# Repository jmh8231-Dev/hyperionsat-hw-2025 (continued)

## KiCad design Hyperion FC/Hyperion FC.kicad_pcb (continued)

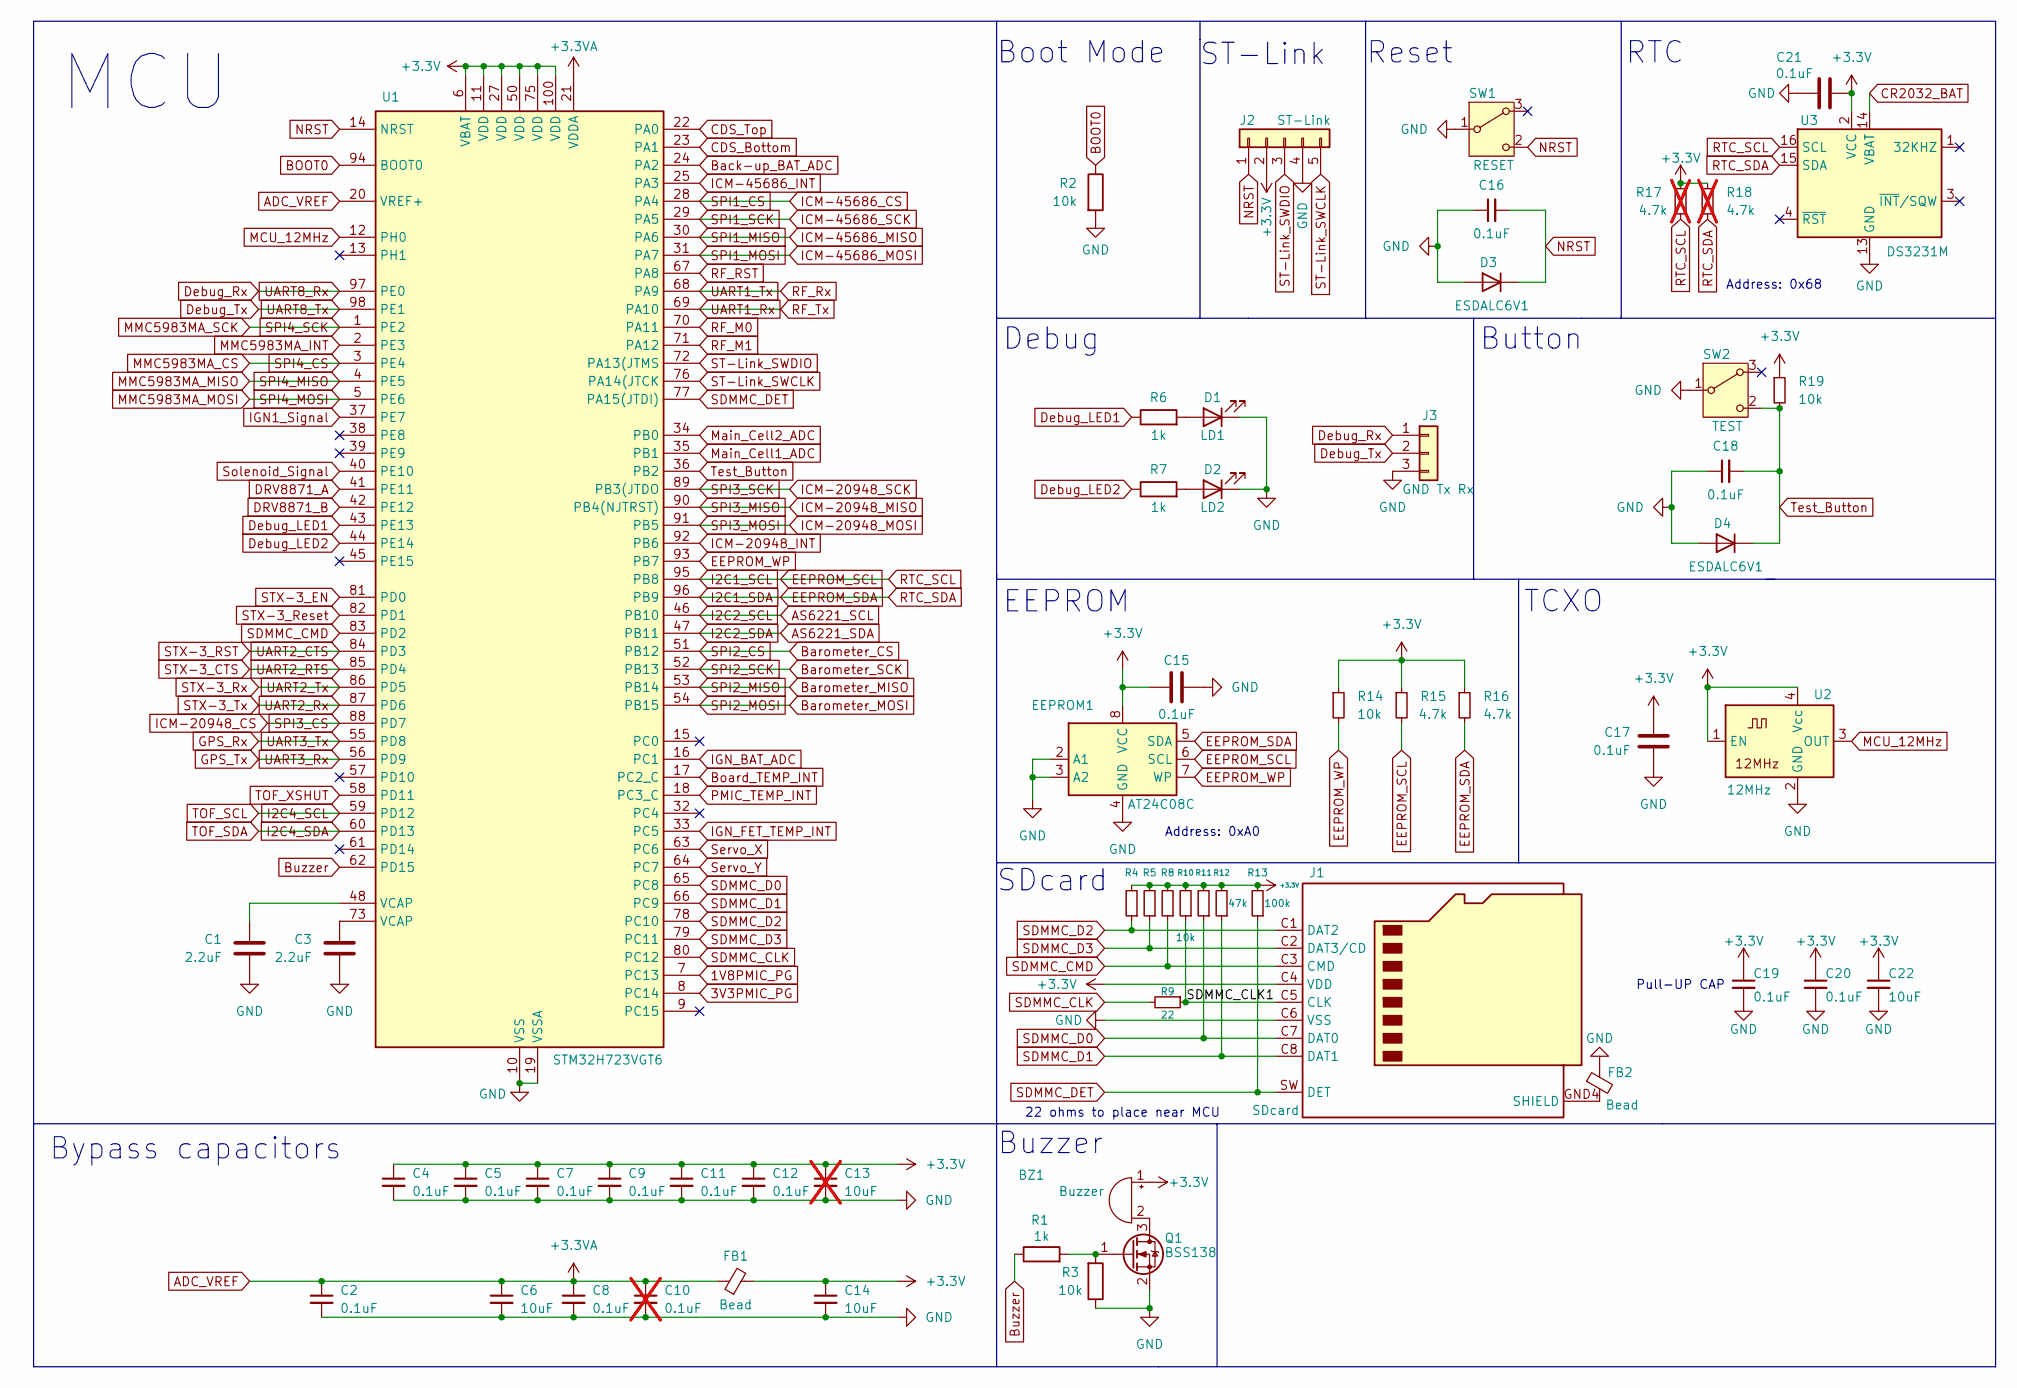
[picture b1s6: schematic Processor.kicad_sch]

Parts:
BZ1: Buzzer; XDCR_SMTB-0827-TW-R
C1, C3: 2.2uF; C_0603_1608Metric
C2, C4, C5, C7, C8, C9, C11, C12, C15, C16, C17, C18, C19, C20, C21: 0.1uF; C_0603_1608Metric
C6, C14, C22: 10uF; C_0805_2012Metric
C10: 0.1uF; C_0603_1608Metric; not fitted
C13: 10uF; C_0805_2012Metric; not fitted
D1: LD1; LED_0805_2012Metric
D2: LD2; LED_0805_2012Metric
D3, D4: ESDALC6V1; D_SOD-882D
EEPROM1: AT24C08C; SOIC-8_3.9x4.9mm_P1.27mm
FB1, FB2: Bead; L_0603_1608Metric
J1: SDcard; JAE_ST1W008S4TR2000
J2: ST-Link; PinHeader_1x05_P2.54mm_Vertical
J3: GND Tx Rx; PinHeader_1x03_P2.54mm_Vertical
Q1: BSS138; SOT-23
R1, R6, R7: 1k; R_0603_1608Metric
R2, R3, R10, R14, R19: 10k; R_0603_1608Metric
R4, R5, R8, R11, R12: 47k; R_0603_1608Metric
R9: 22; R_0402_1005Metric
R13: 100k; R_0603_1608Metric
R15, R16: 4.7k; R_0603_1608Metric
R17, R18: 4.7k; R_0603_1608Metric; not fitted
SW1: RESET; TLSMDT3C020GLFS
SW2: TEST; TLSMDT3C020GLFS
U1: STM32H723VGT6; LQFP-100_14x14mm_P0.5mm
U2: 12MHz; ECS-TXO-2016
U3: DS3231M; SOIC-16W_7.5x10.3mm_P1.27mm

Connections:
1V8PMIC_PG: U1.7 (PC13); also elsewhere on the board
3V3PMIC_PG: U1.8 (PC14); also elsewhere on the board
+3.3V: BZ1.1 (-), C4.1, C5.1, C7.1, C9.1, C11.1, C12.1, C13.1, C14.1, C15.1, C17.1, C19.1, C20.1, C21.2, C22.1, EEPROM1.8 (VCC), FB1.2, J1.C4 (VDD), J2.2, R4.2, R5.2, R8.2, R10.2, R11.2, R12.2, R13.2, R14.1, R15.1, R16.1, R17.1, R18.1, R19.1, U1.6 (VBAT), U1.11 (VDD), U1.27 (VDD), U1.50 (VDD), U1.75 (VDD), U1.100 (VDD), U2.1 (EN), U2.4 (Vcc), U3.2 (VCC); also elsewhere on the board
/Processor/SDMMC_CLK1: J1.C5 (CLK), R9.1, R10.1
ADC_VREF: C2.1, C6.1, C8.1, C10.1, FB1.1, U1.20 (VREF+), U1.21 (VDDA)
AS6221_SCL: U1.46 (PB10); also elsewhere on the board
AS6221_SDA: U1.47 (PB11); also elsewhere on the board
BOOT0: R2.1, U1.94 (BOOT0)
Back-up_BAT_ADC: U1.24 (PA2); also elsewhere on the board
Barometer_CS: U1.51 (PB12); also elsewhere on the board
Barometer_MISO: U1.53 (PB14); also elsewhere on the board
Barometer_MOSI: U1.54 (PB15); also elsewhere on the board
Barometer_SCK: U1.52 (PB13); also elsewhere on the board
Board_TEMP_INT: U1.17 (PC2_C); also elsewhere on the board
Buzzer: R1.1, U1.62 (PD15)
CDS_Bottom: U1.23 (PA1); also elsewhere on the board
CDS_Top: U1.22 (PA0); also elsewhere on the board
CR2032_BAT: U3.14 (VBAT); also elsewhere on the board
DRV8871_A: U1.41 (PE11); also elsewhere on the board
DRV8871_B: U1.42 (PE12); also elsewhere on the board
Debug_LED1: R6.1, U1.43 (PE13)
Debug_LED2: R7.1, U1.44 (PE14)
Debug_Rx: J3.1, U1.97 (PE0)
Debug_Tx: J3.2, U1.98 (PE1)
EEPROM_SCL: EEPROM1.6 (SCL), R15.2, R17.2, U1.95 (PB8), U3.16 (SCL)
EEPROM_SDA: EEPROM1.5 (SDA), R16.2, R18.2, U1.96 (PB9), U3.15 (SDA)
EEPROM_WP: EEPROM1.7 (WP), R14.2, U1.93 (PB7)
GND: C1.2, C2.2, C3.2, C4.2, C5.2, C6.2, C7.2, C8.2, C9.2, C10.2, C11.2, C12.2, C13.2, C14.2, C15.2, C16.1, C17.2, C18.1, C19.2, C20.2, C21.1, C22.2, D1.1 (K), D2.1 (K), D3.2 (A), D4.2 (A), EEPROM1.2 (A1), EEPROM1.3 (A2), EEPROM1.4 (GND), FB2.1, J1.C6 (VSS), J2.4, J3.3, Q1.2 (S), R2.2, R3.1, SW1.1 (B), SW2.1 (B), U1.10 (VSS), U1.19 (VSSA), U1.26 (VSS), U1.49 (VSS), U1.74 (VSS), U1.99 (VSS), U2.2 (GND), U3.5 (GND), U3.6 (GND), U3.7 (GND), U3.8 (GND), U3.9 (GND), U3.10 (GND), U3.11 (GND), U3.12 (GND), U3.13 (GND); also elsewhere on the board
GPS_Rx: U1.55 (PD8); also elsewhere on the board
GPS_Tx: U1.56 (PD9); also elsewhere on the board
I2C4_SCL: U1.59 (PD12); also elsewhere on the board
I2C4_SDA: U1.60 (PD13); also elsewhere on the board
ICM-20948_CS: U1.88 (PD7); also elsewhere on the board
ICM-20948_INT: U1.92 (PB6); also elsewhere on the board
ICM-20948_MISO: U1.90 (PB4(NJTRST)); also elsewhere on the board
ICM-20948_MOSI: U1.91 (PB5); also elsewhere on the board
ICM-20948_SCK: U1.89 (PB3(JTDO); also elsewhere on the board
ICM-45686_CS: U1.28 (PA4); also elsewhere on the board
ICM-45686_INT: U1.25 (PA3); also elsewhere on the board
ICM-45686_MISO: U1.30 (PA6); also elsewhere on the board
ICM-45686_MOSI: U1.31 (PA7); also elsewhere on the board
ICM-45686_SCK: U1.29 (PA5); also elsewhere on the board
IGN1_Signal: U1.37 (PE7); also elsewhere on the board
IGN_BAT_ADC: U1.16 (PC1); also elsewhere on the board
IGN_FET_TEMP_INT: U1.33 (PC5); also elsewhere on the board
MCU_12MHz: U1.12 (PH0), U2.3 (OUT)
MMC5983MA_CS: U1.3 (PE4); also elsewhere on the board
MMC5983MA_INT: U1.2 (PE3); also elsewhere on the board
MMC5983MA_MISO: U1.4 (PE5); also elsewhere on the board
MMC5983MA_MOSI: U1.5 (PE6); also elsewhere on the board
MMC5983MA_SCK: U1.1 (PE2); also elsewhere on the board
Main_Cell1_ADC: U1.35 (PB1); also elsewhere on the board
Main_Cell2_ADC: U1.34 (PB0); also elsewhere on the board
NRST: C16.2, D3.1 (K), J2.1, SW1.2 (C), U1.14 (NRST)
unnamed: BZ1.2 (+), Q1.3 (D)
unnamed: C1.1, U1.48 (VCAP)
unnamed: C3.1, U1.73 (VCAP)
unnamed: D1.2 (A), R6.2
unnamed: D2.2 (A), R7.2
unnamed: FB2.2, J1.GND4 (SHIELD)
unnamed: Q1.1 (G), R1.2, R3.2
PMIC_TEMP_INT: U1.18 (PC3_C); also elsewhere on the board
RF_M0: U1.70 (PA11); also elsewhere on the board
RF_M1: U1.71 (PA12); also elsewhere on the board
RF_RST: U1.67 (PA8); also elsewhere on the board
RF_Rx: U1.68 (PA9); also elsewhere on the board
RF_Tx: U1.69 (PA10); also elsewhere on the board
SDMMC_CLK: R9.2, U1.80 (PC12)
SDMMC_CMD: J1.C3 (CMD), R8.1, U1.83 (PD2)
SDMMC_D0: J1.C7 (DAT0), R11.1, U1.65 (PC8)
SDMMC_D1: J1.C8 (DAT1), R12.1, U1.66 (PC9)
SDMMC_D2: J1.C1 (DAT2), R4.1, U1.78 (PC10)
SDMMC_D3: J1.C2 (DAT3/CD), R5.1, U1.79 (PC11)
SDMMC_DET: J1.SW (DET), R13.1, U1.77 (PA15(JTDI))
ST-Link_SWCLK: J2.5, U1.76 (PA14(JTCK)
ST-Link_SWDIO: J2.3, U1.72 (PA13(JTMS)
STX-3_CTS: U1.85 (PD4); also elsewhere on the board
STX-3_EN: U1.81 (PD0); also elsewhere on the board
STX-3_RST: U1.84 (PD3); also elsewhere on the board
STX-3_Reset: U1.82 (PD1); also elsewhere on the board
STX-3_Rx: U1.86 (PD5); also elsewhere on the board
STX-3_Tx: U1.87 (PD6); also elsewhere on the board
Servo_X: U1.63 (PC6); also elsewhere on the board
Servo_Y: U1.64 (PC7); also elsewhere on the board
Solenoid_Signal: U1.40 (PE10); also elsewhere on the board
TOF_XSHUT: U1.58 (PD11); also elsewhere on the board
Test_Button: C18.2, D4.1 (K), R19.2, SW2.2 (C), U1.36 (PB2)

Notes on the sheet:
Address: 0x68
Bypass capacitors
Address: 0xA0
EEPROM
22 ohms to place near MCU
ST-Link
Buzzer
Boot Mode
RTC
Debug
Button
SDcard
Pull-UP CAP
Reset
MCU
TCXO

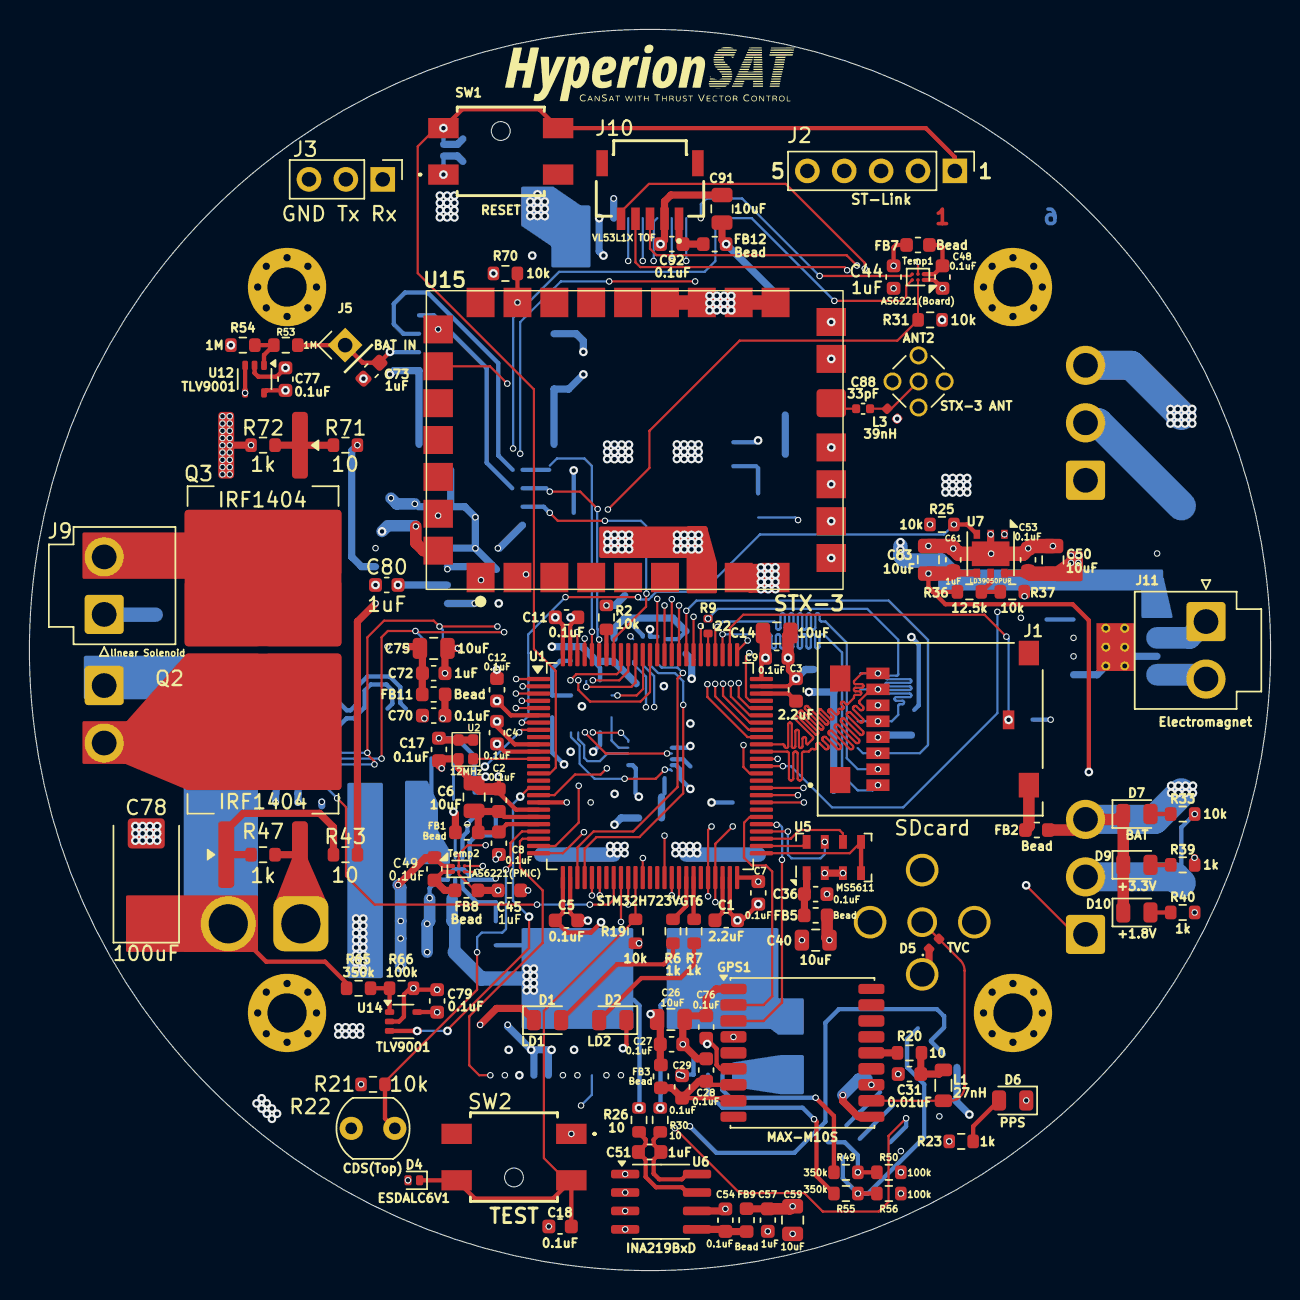
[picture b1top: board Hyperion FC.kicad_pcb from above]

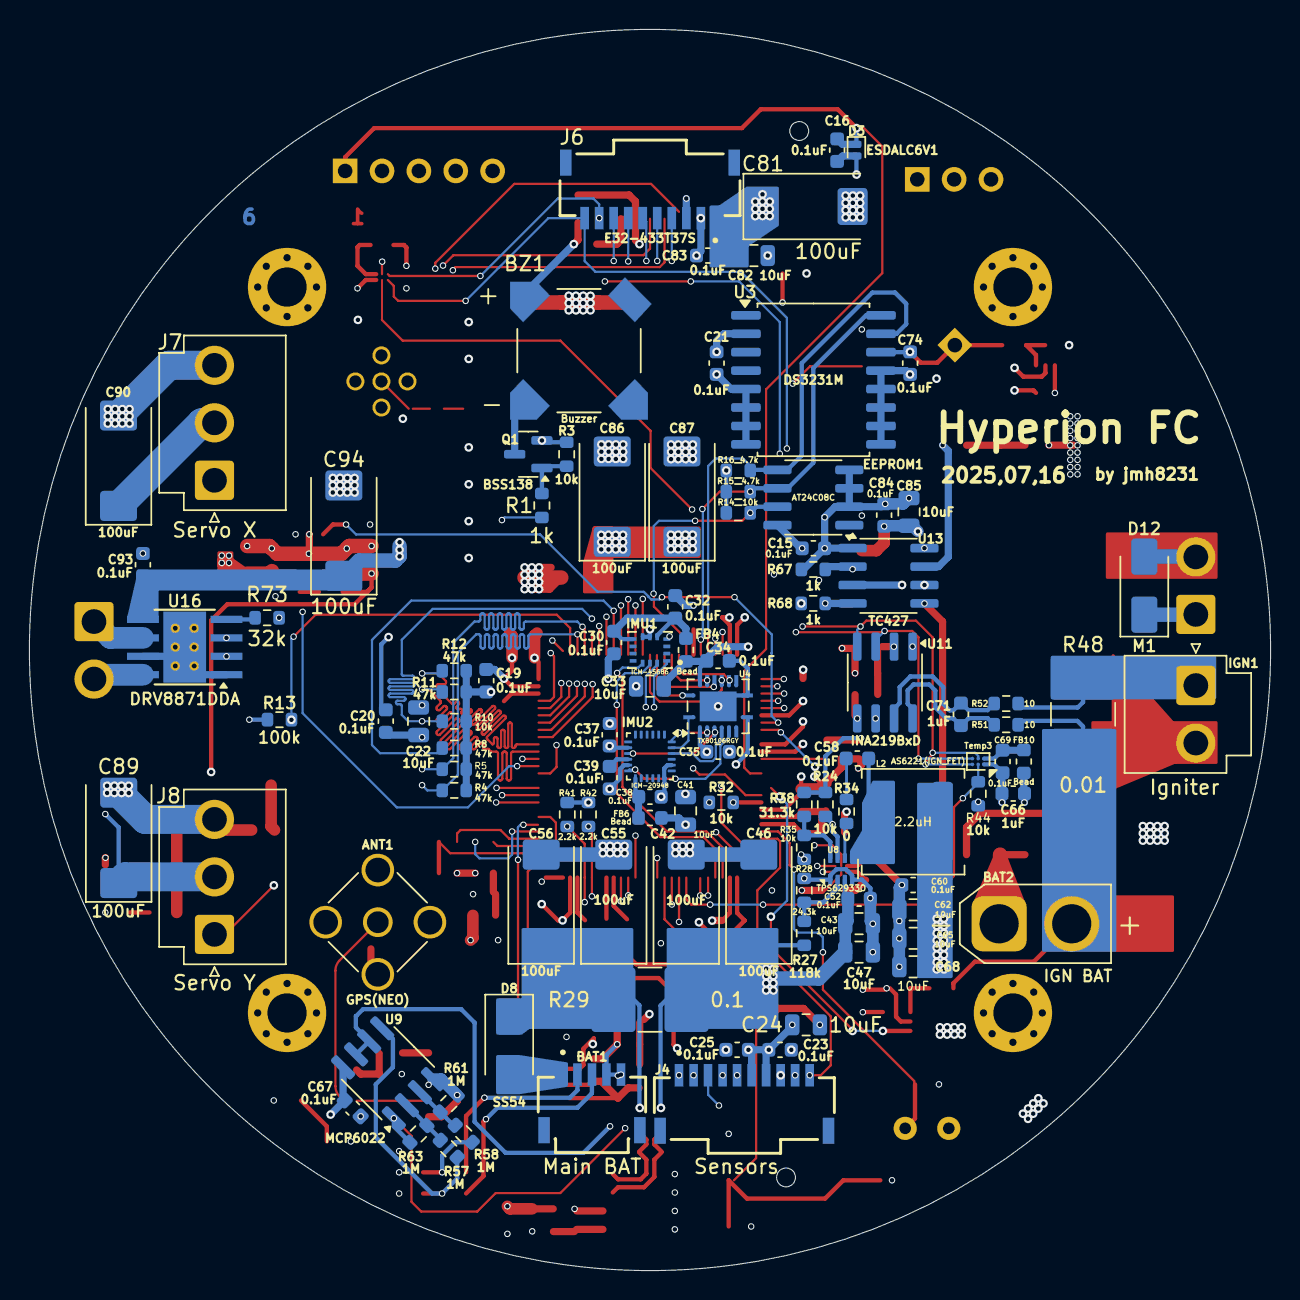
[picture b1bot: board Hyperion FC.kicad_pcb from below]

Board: 6 copper layers, 85.5 x 85.5 mm, 229 parts (107 on the bottom side), 146 nets.

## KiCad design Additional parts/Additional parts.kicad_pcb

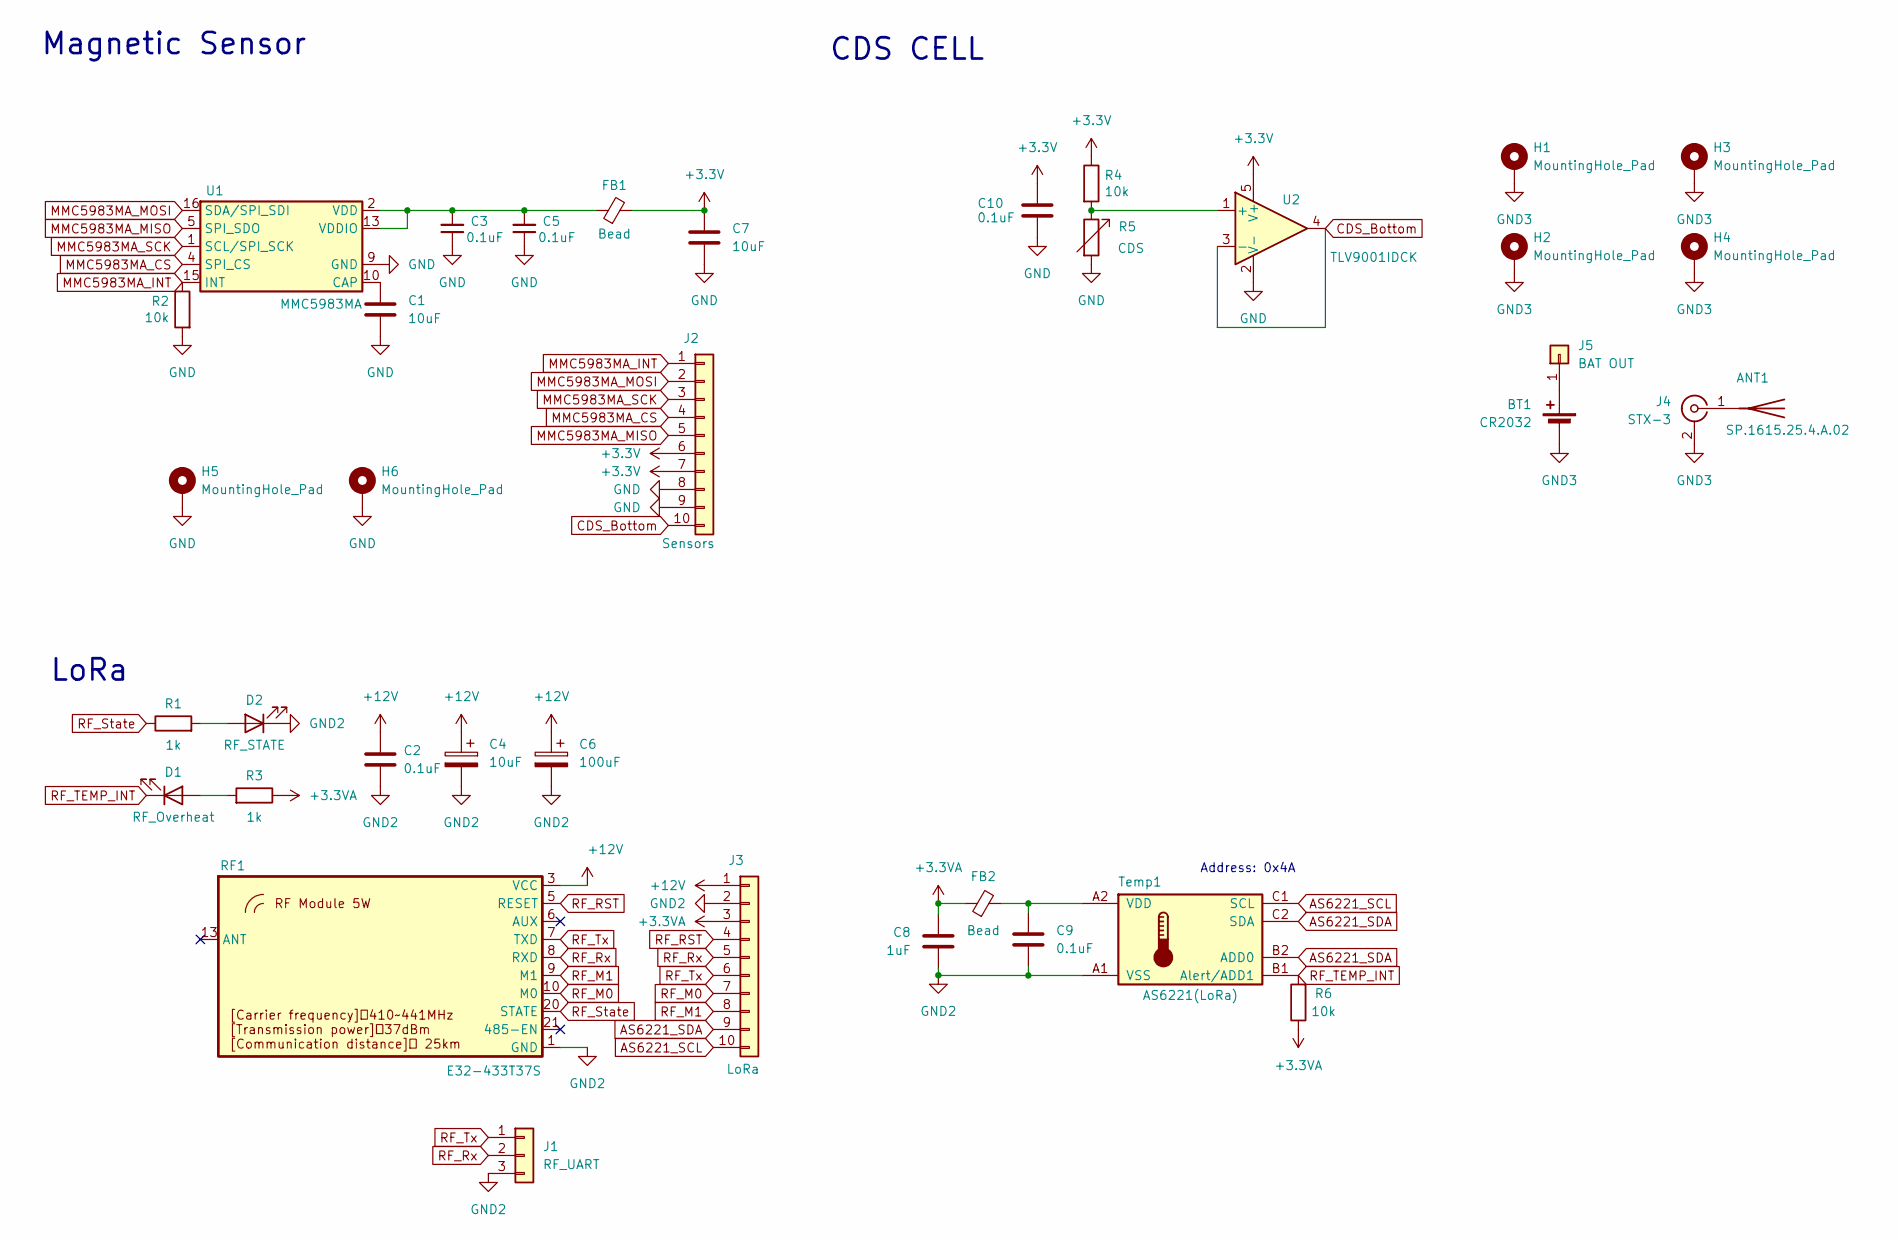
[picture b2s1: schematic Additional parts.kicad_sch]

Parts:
ANT1: SP.1615.25.4.A.02
BT1: CR2032; BAT-HLD-001
C1, C4, C7: 10uF; C_0805_2012Metric
C2, C3, C5, C9, C10: 0.1uF; C_0603_1608Metric
C6: 100uF; CP_EIA-7343-43_Kemet-X
C8: 1uF; C_0603_1608Metric
D1: RF_Overheat; LED_0805_2012Metric
D2: RF_STATE; LED_0805_2012Metric
FB1, FB2: Bead; L_0603_1608Metric
H1, H2, H3, H4, H5, H6: MountingHole_Pad; MountingHole_2.7mm_M2.5_Pad_Via
J1: RF_UART; PinHeader_1x03_P2.54mm_Vertical
J2: Sensors; SAMTEC_T1M-10-F-SH-L-K
J3: LoRa; SAMTEC_T1M-10-F-SH-L-K
J4: STX-3; LINX_CONMMCX001-SMD-T
J5: BAT OUT; PinHeader_1x01_P2.54mm_Vertical
R1, R3: 1k; R_0603_1608Metric
R2, R4, R6: 10k; R_0603_1608Metric
R5: CDS; R_LDR_5.0x4.1mm_P3mm_Vertical
RF1: E32-433T37S
Temp1: AS6221(LoRa); WLCSP-6_1.4x1.0mm_P0.4mm
U1: MMC5983MA; LGA-16_3x3mm_P0.5mm
U2: TLV9001IDCK; SOT-353_SC-70-5

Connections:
+3.3V: C7.1, C10.1, FB1.2, J2.6, J2.7, R4.1, U2.5 (V+)
+3.3VA: C8.2, FB2.1, J3.3, R3.1, R6.1
+12V: C2.1, C4.1, C6.1, J3.1, RF1.3 (VCC), RF1.4 (VCC)
AS6221_SCL: J3.10, Temp1.C1 (SCL)
AS6221_SDA: J3.9, Temp1.B2 (ADD0), Temp1.C2 (SDA)
CDS_Bottom: J2.10, U2.3 (-), U2.4
GND: C1.2, C3.1, C5.1, C7.2, C10.2, H5.1, H6.1, J2.8, J2.9, R2.2, R5.2, U1.9 (GND), U1.11 (GND), U2.2 (V-)
GND2: C2.2, C4.2, C6.2, C8.1, C9.2, D2.1 (K), J1.3, J3.2, RF1.1 (GND), RF1.2 (GND), RF1.11 (GND), RF1.12 (GND), RF1.14 (GND), RF1.15 (GND), RF1.16 (GND), RF1.17 (GND), RF1.18 (GND), RF1.19 (GND), RF1.27 (GND), Temp1.A1 (VSS)
GND3: BT1.2 (-), H1.1, H2.1, H3.1, H4.1, J4.2 (Ext)
MMC5983MA_CS: J2.4, U1.4 (SPI_CS)
MMC5983MA_INT: J2.1, R2.1, U1.15 (INT)
MMC5983MA_MISO: J2.5, U1.5 (SPI_SDO)
MMC5983MA_MOSI: J2.2, U1.16 (SDA/SPI_SDI)
MMC5983MA_SCK: J2.3, U1.1 (SCL/SPI_SCK)
unnamed: ANT1.1 (A), J4.1 (In)
unnamed: BT1.1 (+), J5.1
unnamed: D1.2 (A), R3.2
unnamed: D2.2 (A), R1.2
unnamed: C9.1, FB2.2, Temp1.A2 (VDD)
unnamed: C1.1, U1.10 (CAP)
unnamed: C3.2, C5.2, FB1.1, U1.2 (VDD), U1.13 (VDDIO)
unnamed: R4.2, R5.1, U2.1 (+)
RF_M0: J3.7, RF1.10 (M0)
RF_M1: J3.8, RF1.9 (M1)
RF_RST: J3.4, RF1.5 (RESET)
RF_Rx: J1.2, J3.5, RF1.8 (RXD)
RF_State: R1.1, RF1.20 (STATE)
RF_TEMP_INT: D1.1 (K), R6.2, Temp1.B1 (Alert/ADD1)
RF_Tx: J1.1, J3.6, RF1.7 (TXD)

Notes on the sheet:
Address: 0x4A
LoRa
Magnetic Sensor
CDS CELL

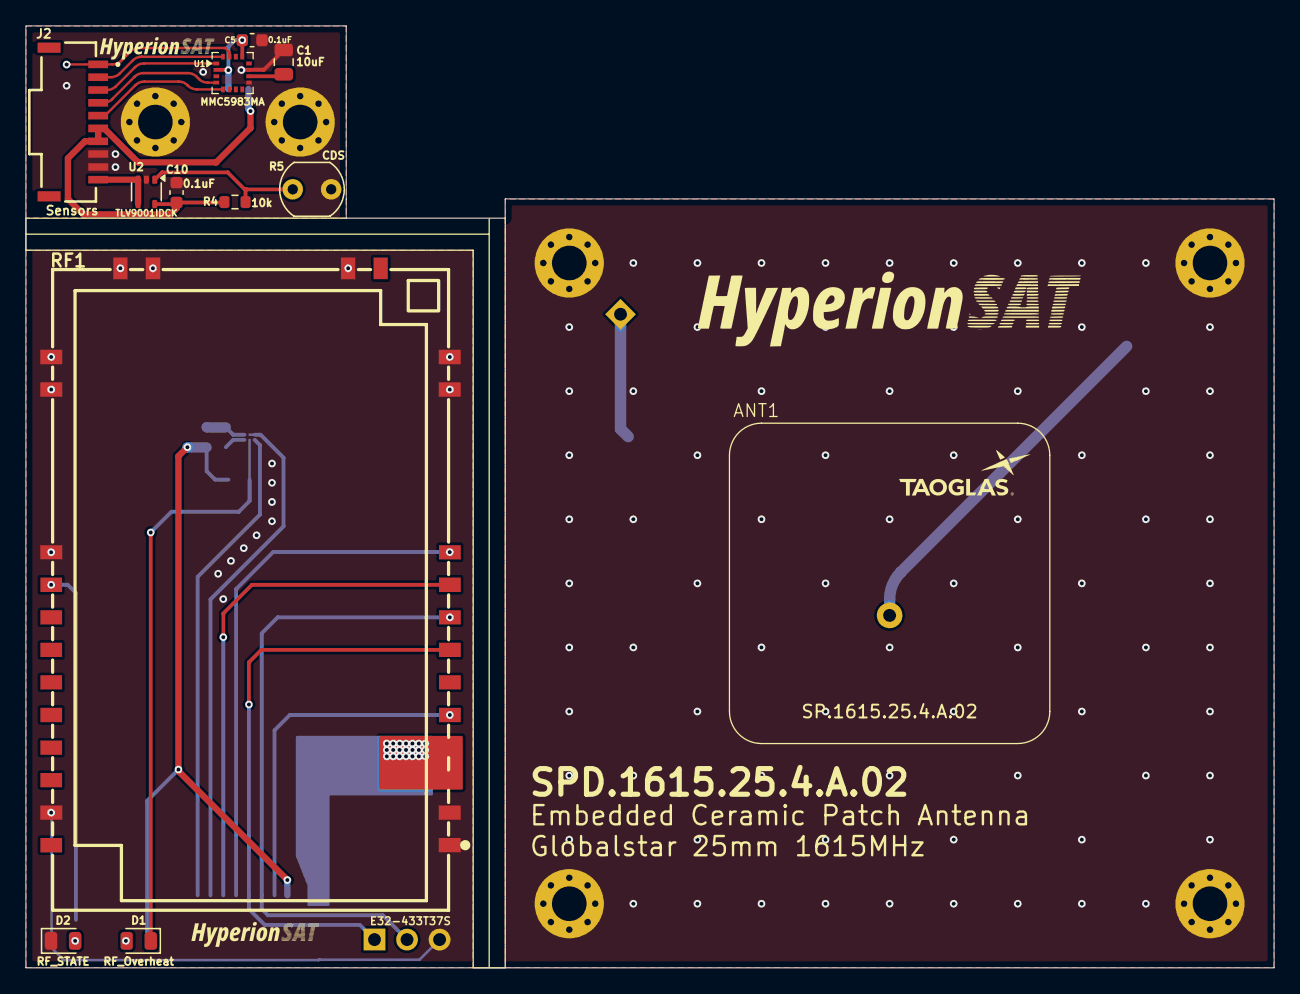
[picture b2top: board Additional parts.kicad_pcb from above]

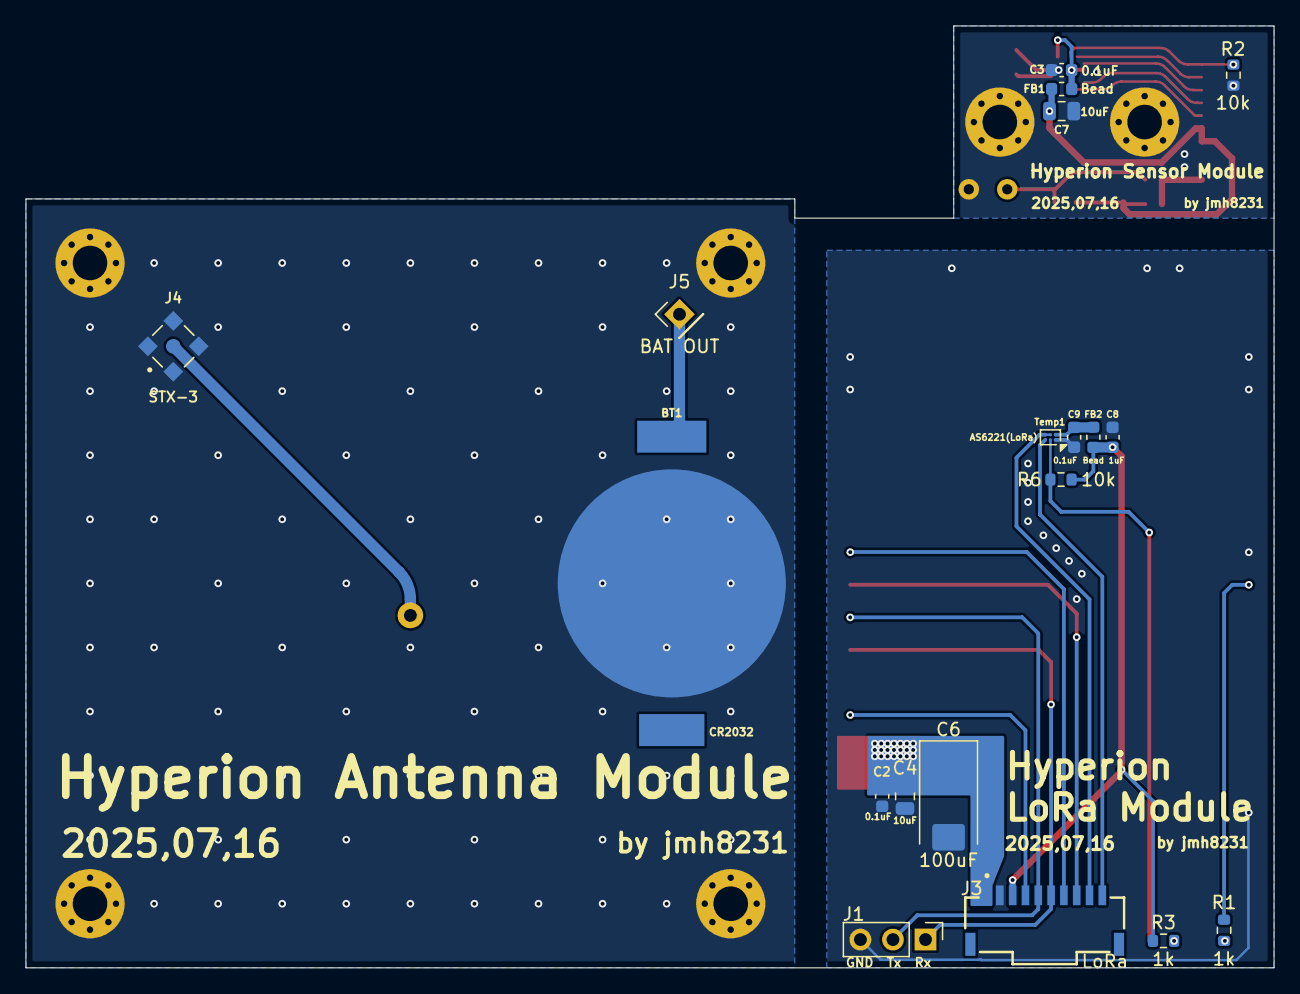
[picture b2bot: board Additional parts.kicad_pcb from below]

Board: 2 copper layers, 97.4 x 73.5 mm, 37 parts (19 on the bottom side), 29 nets.

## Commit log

2025-08-20 HyperionSAT Add-on
2025-08-20 HyperionSAT FC v1.2
2025-08-20 RedCheck-SDRAM Board v1.0
2025-08-21 sch pdf 추가
2025-08-24 img update
2026-01-06 add img
